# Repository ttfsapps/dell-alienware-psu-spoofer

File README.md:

# Dell/Alienware PSU Spoofer 
Allows user to use any lab power supply to power a Dell or Alienware notebook pc by supplying the required Dell PSU ID string. Dell and Alienware computers require the ID string to run normally. Performance is throttled if no ID string is provided for power protection purposes. The spoofer is configurable to send the ID string that matches the input lab supply's power rating via dipswitches. 

## Hardware Required
Custom PCB design which uses an Atmel ATtiny85 microcontroller and OneWireHub to emulate a Maxim DS2502, a 1Kb Add-Only Memory device with a unique 48-bit serial number, programmable EPROM, and 1-Wire interface. The DS2502 is used by Dell and Alienware OEM PSU's to determine the PSU's wattage. It appears that the notebook pc's do not use any of the other information provided in the Dell ID string other than wattage.

## KiCad Files
[KiCad Schematic](kicad/dell_psu_spoofer.kicad_sch)

[KiCad PCB](kicad/dell_psu_spoofer.kicad_pcb)

[KiCad BOM](kicad/dell_psu_spoofer.csv)

[Gerber File](kicad/dell_psu_spoofer.kicad_pcb.zip)

## Libraries Required
|Library|Function|
|:-----:|:-----:|
|[OneWireHub.h](https://github.com/orgua/OneWireHub)|OneWireHub library| 
|DS2502.h|included with OneWireHub library| 

## DIP Switch Settings
|A|B|C|Watts|
|:-----:|:--------:|:-------:|:-----:|
|0|0|0|75|
|0|0|1|100|
|0|1|0|125|
|0|1|1|150|
|1|0|0|175|
|1|0|1|200|
|1|1|0|225|
|1|1|1|250|

## Pin Names, Numbers, and Functions
|||||||||
|:--:|:--:|:--:|:--:|:--:|:--:|:--:|:--:|
|ATtiny85 Pin|5|1|7|6|3|2|ATtiny85 hardware pin numbers (reference only)|
|Pin Name|PB0|PB5/RST|PB2|PB1|PB4|PB3|ATtiny85/Arduino pin names|
|Arduino Pin #|0|5|2|1|4|3|Arduino IDE pin numbers (s/w uses these)|
|PCB Label|LED|RST|ID|A|B|C|Pin function|
|Function||not used|OneWire|Power Select|Power Select|Power Select|

TTFS Apps 2026

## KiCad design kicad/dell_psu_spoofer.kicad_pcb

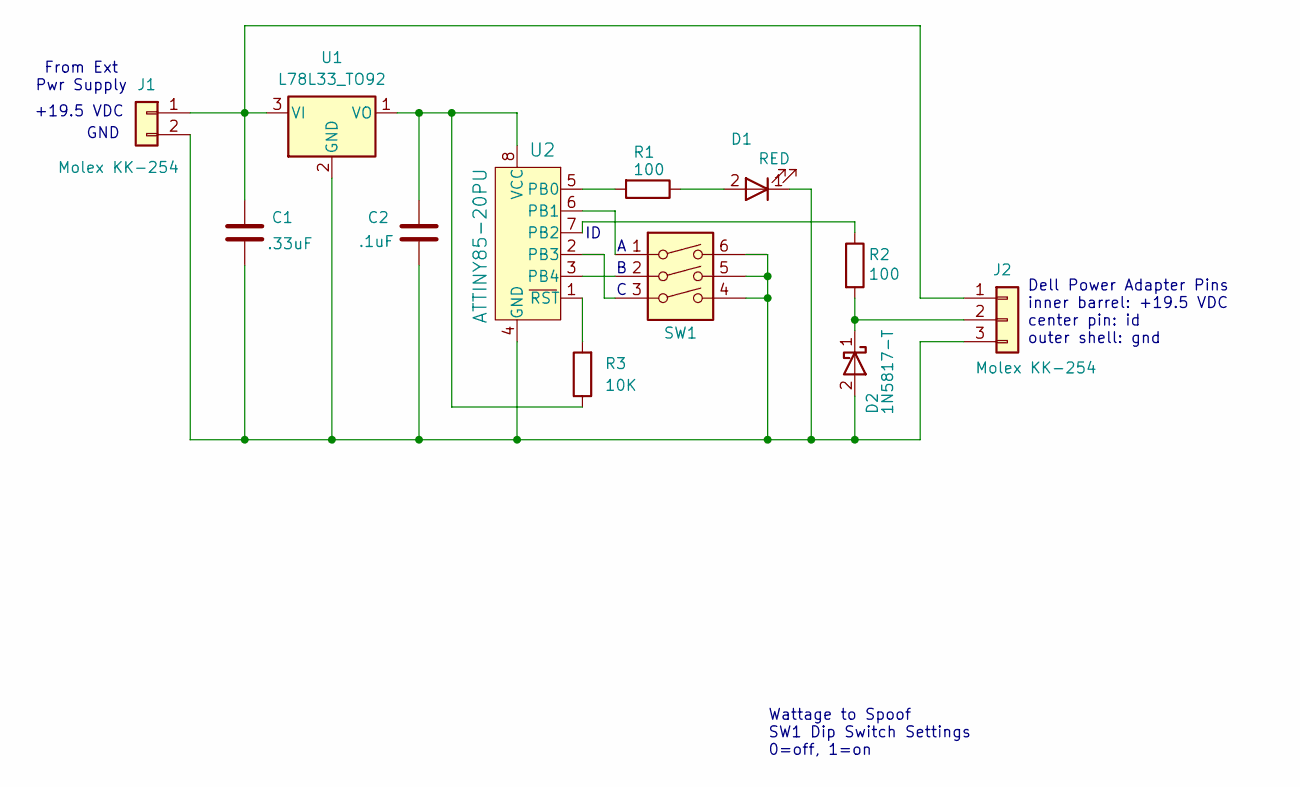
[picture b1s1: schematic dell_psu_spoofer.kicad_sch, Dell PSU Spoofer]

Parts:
C1: .33uF; C_Disc_D3.0mm_W1.6mm_P2.50mm
C2: .1uF; C_Disc_D3.0mm_W1.6mm_P2.50mm
D1: RED; LED_D1.8mm_W3.3mm_H2.4mm
D2: 1N5817-T; D_DO-41_SOD81_P10.16mm_Horizontal
J1: Molex KK-254; KK-254 CONN HEADER RA 2POS 2.54MM
J2: Molex KK-254; KK-254 CONN HEADER RA 3POS 2.54MM
R1, R2: 100; R_Axial_DIN0207_L6.3mm_D2.5mm_P7.62mm_Horizontal
R3: 10K; R_Axial_DIN0207_L6.3mm_D2.5mm_P7.62mm_Horizontal
SW1: SW_DIP_x04; SW_DIP_SPSTx03_Slide_6.7x9.18mm_W7.62mm_P2.54mm_LowProfile
U1: L78L33_TO92; TO-92_Inline
U2: ATTINY85-20PU; DIP-8_W7.62mm_Socket; MPN ATTINY85-20PU; Digi-Key_PN ATTINY85-20PU-ND

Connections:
unnamed: D1.2 (A), R1.1
unnamed: C1.2, C2.2, D1.1 (K), D2.2 (A), J1.2, J2.3, SW1.4, SW1.5, SW1.6, U1.2 (GND), U2.4 (GND)
unnamed: D2.1 (K), J2.2, R2.2
unnamed: C1.1, J1.1, J2.1, U1.3 (VI)
unnamed: C2.1, R3.1, U1.1 (VO), U2.8 (VCC)
unnamed: R1.2, U2.5 (PB0)
unnamed: SW1.1, U2.6 (PB1)
unnamed: R2.1, U2.7 (PB2)
unnamed: SW1.3, U2.2 (PB3)
unnamed: SW1.2, U2.3 (PB4)
unnamed: R3.2, U2.1 (RST)

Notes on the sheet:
Dell Power Adapter Pins inner barrel: +19.5 VDC center pin: id outer shell: gnd
+19.5 VDC
From Ext Pwr Supply
GND
Wattage to Spoof SW1 Dip Switch Settings 0=off, 1=on

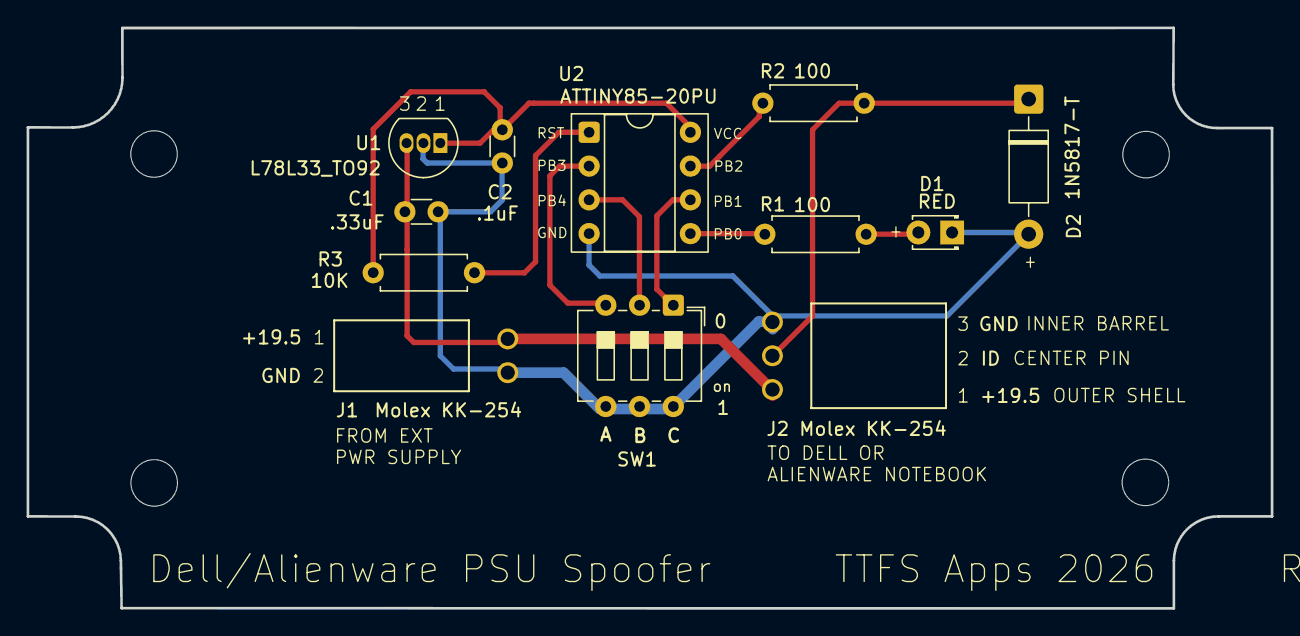
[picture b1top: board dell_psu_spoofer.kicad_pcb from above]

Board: 2 copper layers, 93.6 x 43.7 mm, 12 parts (0 on the bottom side), 11 nets.

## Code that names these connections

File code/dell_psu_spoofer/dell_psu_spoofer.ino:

// ****************************************************************************************
// Dell/Alienware PSU Spoofer 
//
// Allows any lab power supply to operate correctly with a Dell or Alienware notebook.
// The spoofer is configurable to send the ID string that matches the input lab supply's 
// power rating.

// Uses OneWireHub to emulate a Maxim DS2502, a 1Kb Add-Only Memory device 
// with a unique 48-bit serial number, programmable EPROM, and 1-Wire interface.
//
// KiCad Files
// dell_psu_spoofer.kicad_sch
// dell_psu_spoofer.kicad_pcb
//
// Version 0.0   initial release for rev 0.0 pcb only
// Version 0.1   inverted logic to use internal pullup resistors of attiny85 - reliability
//               swapped pb5 and pb1 for c dipswitch pin to avoid rst conflict
//               requires rev 0.1 pcb or later
//               reduced min wattage and max wattage to 75W and 250W
//
// TTFS Apps 2026
// ****************************************************************************************

// ****************debug macros*************************
#define DEBUG 0   // 1 = enable debug, 0 = disable debug

#if DEBUG
  #define DEBUG_BEGIN(baud)   Serial.begin(baud)
  #define DEBUG_PRINT(x)      Serial.print(x)
  #define DEBUG_PRINTLN(x)    Serial.println(x)
#else
  #define DEBUG_BEGIN(baud)   do {} while(0)
  #define DEBUG_PRINT(x)      do {} while(0)
  #define DEBUG_PRINTLN(x)    do {} while(0)
#endif
// ****************debug macros*************************

// onewirehub emulates numerous devices including the ds2502 used by dell/alienware psu's
#include <OneWireHub.h> // onewire hub library https://github.com/orgua/OneWireHub
#include "DS2502.h"     // included with onewirehub library

// DIP Switch Settings
// A   B   C	WATTS
// ----------------
// 0   0   0   75
// 0   0   1   100
// 0   1   0   125
// 0   1   1   150
// 1   0   0   175
// 1   0   1   200
// 1   1   0   225
// 1   1   1   250

// Pin Names, Numbers, and Functions
// ATtiny Pin #       5      1      7      6      3      2      // ATtiny85 hardware pin numbers (reference only)
// Pin Name          PB0  PB5/RST  PB2    PB1    PB4    PB3     // ATtiny85/Arduino pin names
// Arduino Pin #      0      5      2      1      4      3      // Arduino IDE pin numbers (s/w uses these)
// Function          LED    RST    ID      A      B      C      // Pin function
//                          NOT    ONE    PWR    PWR    PWR
//                          USED   WIRE   SEL    SEL    SEL

// declare pins
constexpr uint8_t idPin{2};   // PB2 dell id
constexpr uint8_t ledPin{0};  // PB0 led

// create onewire hub
auto hub = OneWireHub(idPin);                             

// DS2502( family_code,  serial_1,  serial_2,  serial_3,  serial_4,  serial_5,  serial_6 );
auto dellPSURom = DS2502(0x09, 0x00, 0x00, 0x02, 0x25, 0x0D, 0x00); 

void setup() {

  // ******************
  // set up the spoofer
  // ******************

  // ************ debug code *************
  // verify 8mhz operation It should print: 8000000
  // If it prints 1000000, the attiny fuses aren't blown
  // and timing will fail.
  DEBUG_BEGIN(115200);   // serial baud rate
  DEBUG_PRINTLN(F_CPU);  // output attiny85 clock frequency
  // ************ debug code *************

  // declare pins
  constexpr uint8_t aPin{1};    // PB5 first bit of pwr select
  constexpr uint8_t bPin{4};    // PB4 second bit of pwr select
  constexpr uint8_t cPin{3};    // PB3 third bit of pwr select

  // dell id string parts
  String header = "DELL00AC";                                  // Dell ID header   DELL00AC
  String volts = "195";                                        // Volts*10         VVV 3 digits in tenths of volts eg. 19.5 = 195
  String watts = "075100125150175200225250";                   // Watts            WWW 3 digits
  String amps = "038051064077090103115128";                    // Amps*10          III 3 digits in tenths of amps eg. 5.1 = 051
  String serialNumber = "CN0123456789ABCDEA05";                // Serial number    CN0123456789ABCDEA05 random 23 character
  String dellPSUId = "DELL00ACWWWVVVIIICN0123456789ABCDEA05";  // Dell ID          DELL00ACWWWVVVIIICN0123456789ABCDEA05 40 characters
  char outBuffer[42] = "";                                     // dell id string + two crc bytes

  // set led pin
  pinMode(ledPin, OUTPUT);  // led

  // set onewire connection
  pinMode(idPin, INPUT);  // input mode, don't use internal pull-up resistor

  // set sense pins  for dip switch to digital input mode using internal pull up
  // note: rev 1 implements pull up logic
  pinMode(aPin, INPUT_PULLUP);  // first bit of pwr select
  pinMode(bPin, INPUT_PULLUP);  // second bit of pwr select
  pinMode(cPin, INPUT_PULLUP);  // third bit of pwr select

  // Fetch DIP Switch Settings new hardware inverts logic
  // calculate pointer to selected power based on aPin, bPin, and cPin vals
  uint8_t ptr = 4 * !digitalRead(aPin) + 2 * !digitalRead(bPin) + !digitalRead(cPin);
 
  // Build the identification string
  dellPSUId = header + watts.substring(ptr, ptr + 2) + volts + amps.substring(ptr, ptr + 2) + serialNumber;

  // Pad if needed
  while (dellPSUId.length() < 40) dellPSUId += ' ';

  // Calculate CRC
  uint16_t crc = crc16_arc_string(dellPSUId);

  uint8_t lowByte = crc & 0xFF;          // first CRC byte (little-endian)
  uint8_t highByte = (crc >> 8) & 0xFF;  // second CRC byte

  // Append raw crc bytes to the String (they may be non-printable!)
  // the crc bytes have to be in little-endian order
  // there is some debate as to whether all dell models use crc
  // now the string is 42 bytes long
  dellPSUId += (char)lowByte;           // second byte goes first
  dellPSUId += (char)highByte;          // first byte goes second

  // set up id string and stuff fake eeprom device
  dellPSUId.toCharArray(outBuffer, 42);
  dellPSURom.writeMemory((uint8_t *)outBuffer, 42, 0x00);

  // attach fake device to onewire hub
  hub.attach(dellPSURom);

}

void loop() {

  // ********************
  // start up the spoofer
  // ********************

  // signal life
  digitalWrite(ledPin, HIGH);  // LED on

  // onewirehub does all the hard work
  // Detects reset pulse from laptop
  // Answers presence
  // Handles Skip ROM (0xCC — Dell almost always uses this)
  // Responds to Read Memory (0xF0)
  // Provides bytes from the emulated memory 
  hub.poll();

}

uint16_t crc16_arc_string(const String &str) {

  // ******************************
  // routine tocalculate CRC-16/ARC
  // ******************************

  uint16_t crc = 0;                           // Start with crc = 0x0000

  // calculate crc
  // For each byte in the 40-byte string
  for (size_t i = 0; i < str.length(); i++) { 
    
    uint8_t byte = (uint8_t)str[i];           // fetch byte
    crc ^= (uint16_t)byte << 8;               // XOR the byte into the upper 8 bits
    
    // For each byte in the 40-byte str of crc (crc ^= byte << 8)
    for (uint8_t bit = 0; bit < 8; bit++) {   

    // If the current MSB (bit 15) is 1
      if (crc & 0x8000) {
        crc = (crc << 1) ^ 0x8005;            // then shift left 1 bit, then XOR with 0x8005
      } else {
        crc <<= 1;                            // else just shift left 1 bit
      }
    }

  }

  // return crc
  return crc;
}

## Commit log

2026-03-17 Draft in Progress
    Expanded README with hardware requirements, libraries, DIP switch settings, and pin functions.
2026-03-17 Draft in Progress
    Updated README to improve clarity and organization of hardware and software information.
2026-03-22 Draft in Progress
    Added links and images for KiCad files and BOM.
2026-04-18 Lowered power settings
2026-04-18 Lower power ranges
2026-04-18 Update DIP switch settings wattage values
